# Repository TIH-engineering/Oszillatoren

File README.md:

# LA – Oszillatoren

## 🔌 Leiterplattenbeschreibung

Die Leiterplatte **LA – Oszillatoren** wurde für Laborübungen im Bereich
Elektronik und Hardwareentwicklung entwickelt. Sie ermöglicht die praktische
Untersuchung unterschiedlicher Oszillatorschaltungen und den Vergleich ihrer
Funktionsprinzipien und Eigenschaften.

Auf einer gemeinsamen Leiterplatte sind mehrere typische Oszillatorschaltungen
realisiert:

- **RC-Phasenschieber-Oszillator**
- **Wien-Brücken-Oszillator**
- **OPV-Relaxationsoszillator**
- **RC-/Quarzoszillatoren**

Die Schaltungen sind räumlich voneinander getrennt aufgebaut und verfügen über
gut zugängliche Messpunkte. Dadurch können charakteristische Signale direkt mit
dem Oszilloskop untersucht und mit den theoretisch berechneten Größen verglichen
werden.

Bei ausgewählten Schaltungen sind Bauteile steck- bzw. austauschbar ausgeführt.
Damit können beispielsweise unterschiedliche Widerstandswerte eingesetzt und
deren Einfluss auf Frequenz und Schwingverhalten experimentell untersucht werden.

Die Leiterplatte wird mit **+5 V / GND / −5 V** versorgt. Die einzelnen
Messpunkte und Anschlüsse sind direkt auf der Leiterplatte beschriftet.

> **Einsatzgebiet:** Laborunterricht zur Untersuchung von Oszillatoren,
> Schwingbedingungen, Frequenzbestimmung und dem Einfluss einzelner Bauteile.

---

# 📥 Downloads

| Datei | Beschreibung |
|:------|:-------------|
| 📄 Schaltplan (PDF) | [`schematic.pdf`](../../releases/latest/download/schematic.pdf) |
| 🖨 Leiterplatte (PDF) | [`pcb.pdf`](../../releases/latest/download/pcb.pdf) |
| 🔩 Bohrplan | [`drill.pdf`](../../releases/latest/download/drill.pdf) |
| 📋 Stückliste (Excel) | [`bom.xlsx`](../../releases/latest/download/bom.xlsx) |
| 🌐 Interactive BOM | [`ibom.html`](../../releases/latest/download/ibom.html) |
| 📦 Fertigungsdaten | [`kicad.zip`](../../releases/latest/download/kicad.zip) |
| 🧊 STEP-Modell | [`pcb.step`](../../releases/latest/download/pcb.step) |

---

# 🖥 Leiterplatte

## Vorschau

| Oberseite | Unterseite |
|:---------:|:----------:|
|  |  |

## Oberseite

## Unterseite

---

# ℹ Projektinformationen

| Eigenschaft | Wert |
|--------------|------|
| Projekt | LA – Oszillatoren |
| Software | KiCad 10 |
| Repository | TIH-engineering/Oszillatoren |
| Lizenz | CC BY-NC-SA 4.0 |

---

# 🚀 Releases

Jeder Release enthält automatisch:

- Gerberdaten
- Bohrdaten
- Stückliste (Excel)
- Interactive BOM
- STEP-Modell
- Schaltplan als PDF
- Leiterplatte als PDF
- 3D-Renderings

Die jeweils aktuelle Version befindet sich unter **Releases**.

---

# 👨‍🏫 Autor

**HTL Rankweil**  
Labor Elektronik / Hardwareentwicklung

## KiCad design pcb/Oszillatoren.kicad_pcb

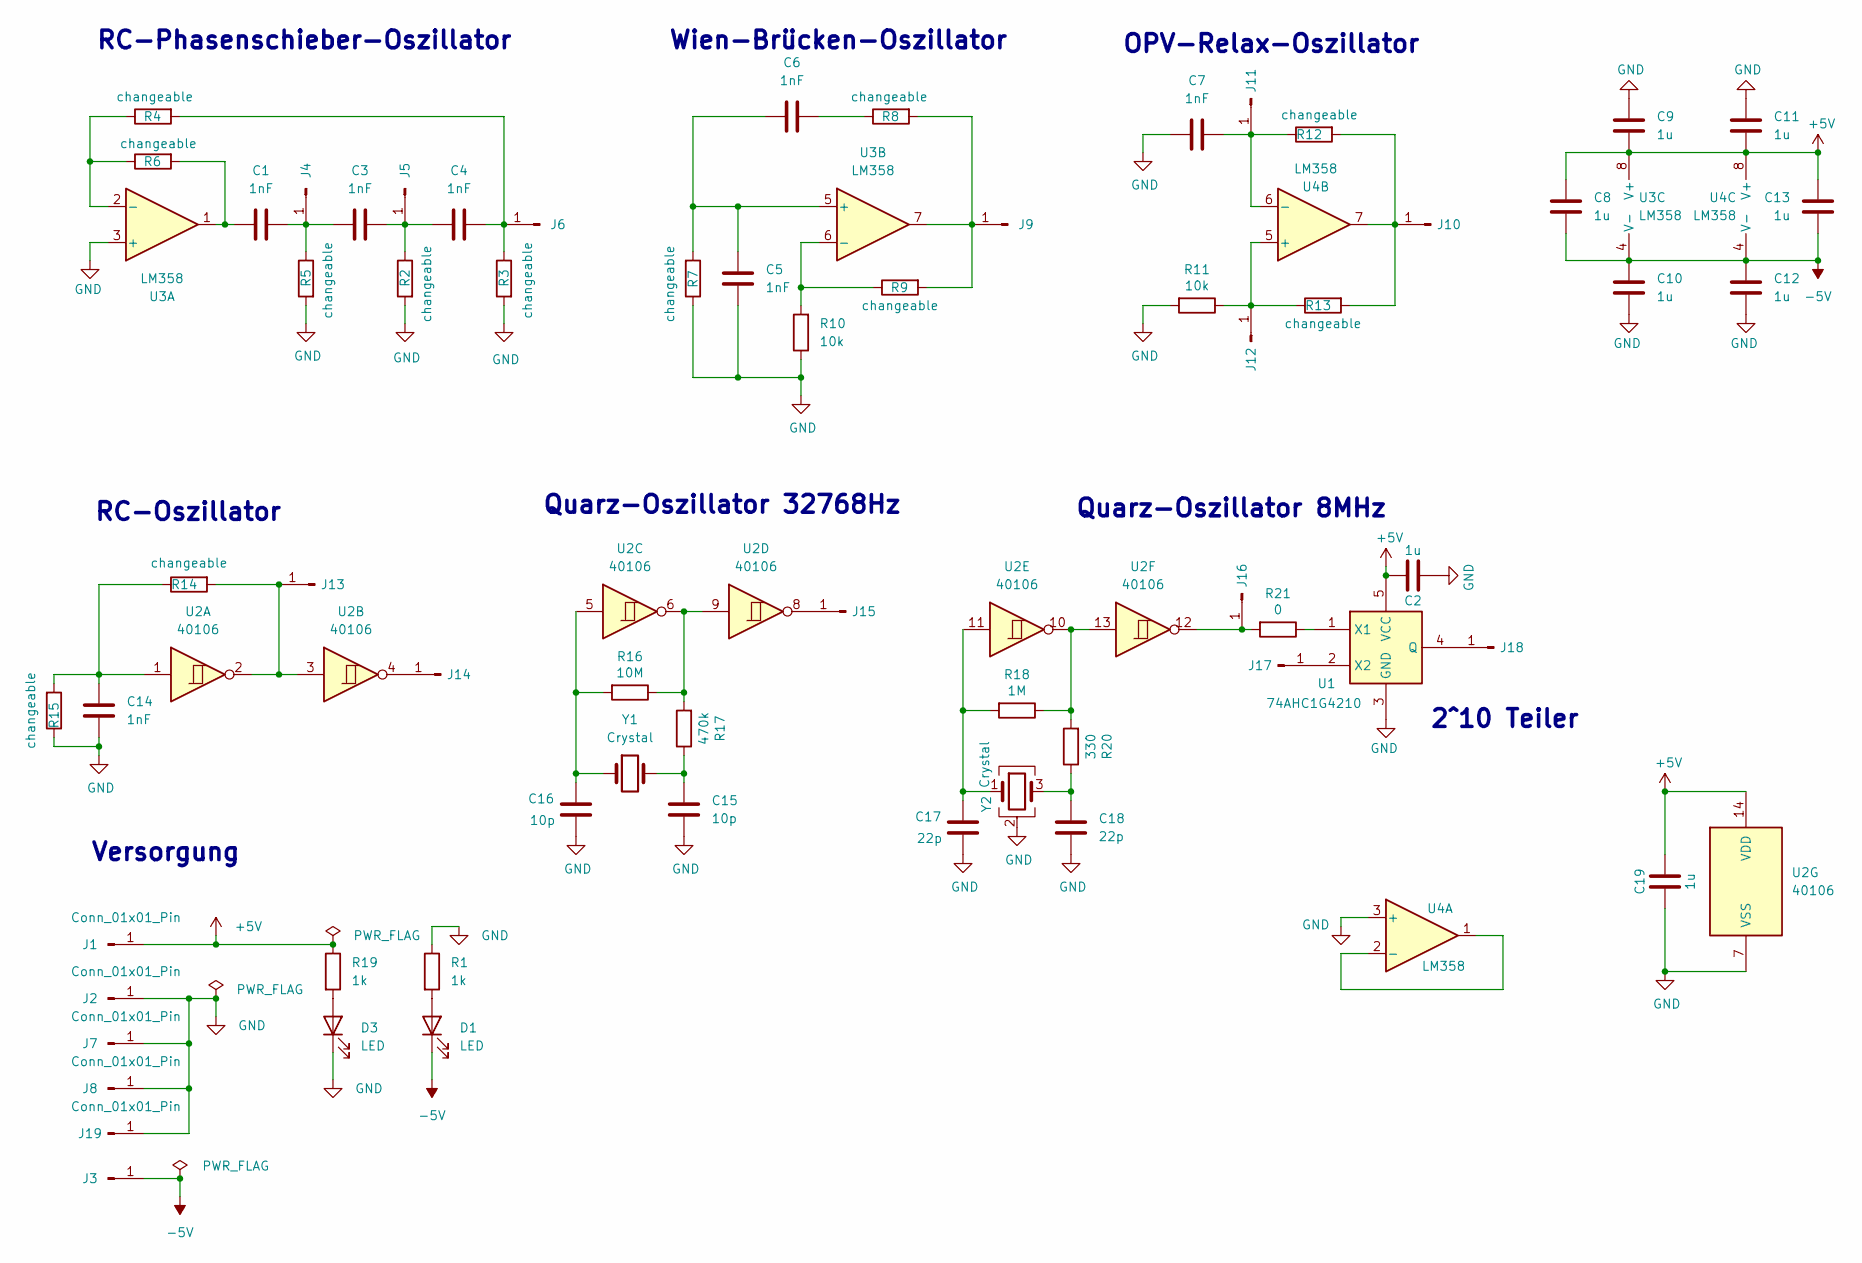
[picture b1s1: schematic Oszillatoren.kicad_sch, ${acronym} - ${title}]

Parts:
C1, C3, C4, C5, C6, C7, C14: 1nF; C_0805_2012Metric
C2, C8, C9, C10, C11, C12, C13, C19: 1u; C_1206_3216Metric
C15, C16: 10p; C_0603_1608Metric
C17, C18: 22p; C_0603_1608Metric
D1, D3: LED; LED_1206_3216Metric
J1, J2, J3, J4, J5, J6, J7, J8, J9, J10, J11, J12, J13, J14, J15, J16, J17, J18, J19: Conn_01x01_Pin; PinHeader_1x01_P2.54mm_Vertical
R1, R19: 1k; R_1206_3216Metric
R2, R3, R4, R5, R6, R7, R8, R9, R12, R13, R14, R15: 10k; R_axial_SMD-Adapter_P10.16mm_1mm
R10, R11: 10k; R_0805_2012Metric
R16: 10M; R_0805_2012Metric
R17: 470k; R_0805_2012Metric
R18: 1M; R_0805_2012Metric
R20: 330; R_0805_2012Metric
R21: 0; R_0805_2012Metric
U1: 74AHC1G4210; SOT-353_SC-70-5
U2: 40106; DIP-14_W7.62mm
U3, U4: LM358; DIP-8_W7.62mm
Y1: Crystal; Crystal_SMD_G8-2Pin_3.2x1.5mm_HandSoldering
Y2: Crystal; Crystal_SMD_EuroQuartz_MQ-4Pin_7.0x5.0mm_HandSoldering

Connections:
+5V: C2.1, C8.1, C9.1, C11.2, C13.1, C19.1, J1.1 (Pin_1_1), R19.1, U1.5 (VCC), U2.14 (VDD), U3.8 (V+), U4.8 (V+)
-5V: C8.2, C10.2, C12.1, C13.2, D1.1 (K), J3.1 (Pin_1_1), U3.4 (V-), U4.4 (V-)
GND: C2.2, C5.1, C7.2, C9.2, C10.1, C11.1, C12.2, C14.1, C15.2, C16.2, C17.2, C18.2, C19.2, D3.1 (K), J2.1 (Pin_1_1), J7.1 (Pin_1_1), J8.1 (Pin_1_1), J19.1 (Pin_1_1), R1.1, R2.2, R3.2, R5.2, R7.1, R10.1, R11.2, R15.1, U1.3 (GND), U2.7 (VSS), U3.3 (+), U4.3 (+), Y2.2 (G), Y2.4 (G)
unnamed: C1.1, R6.2, U3.1
unnamed: C6.2, R8.1
unnamed: C14.2, R14.1, R15.2, U2.1
unnamed: C15.1, R17.1, Y1.2
unnamed: C16.1, R16.2, U2.5, Y1.1
unnamed: C17.1, R18.2, U2.11, Y2.1
unnamed: C18.1, R20.1, Y2.3
unnamed: D1.2 (A), R1.2
unnamed: D3.2 (A), R19.2
unnamed: C1.2, C3.1, J4.1 (Pin_1_1), R5.1
unnamed: C3.2, C4.1, J5.1 (Pin_1_1), R2.1
unnamed: C4.2, J6.1 (Pin_1_1), R3.1, R4.2
unnamed: J9.1 (Pin_1_1), R8.2, R9.2, U3.7
unnamed: J10.1 (Pin_1_1), R12.2, R13.2, U4.7
unnamed: C7.1, J11.1 (Pin_1_1), R12.1, U4.6 (-)
unnamed: J12.1 (Pin_1_1), R11.1, R13.1, U4.5 (+)
unnamed: J13.1 (Pin_1_1), R14.2, U2.2, U2.3
unnamed: J14.1 (Pin_1_1), U2.4
unnamed: J15.1 (Pin_1_1), U2.8
unnamed: J16.1 (Pin_1_1), R21.2, U2.12
unnamed: J17.1 (Pin_1_1), U1.2 (X2)
unnamed: J18.1 (Pin_1_1), U1.4 (Q)
unnamed: R16.1, R17.2, U2.6, U2.9
unnamed: R18.1, R20.2, U2.10, U2.13
unnamed: R21.1, U1.1 (X1)
unnamed: R4.1, R6.1, U3.2 (-)
unnamed: C5.2, C6.1, R7.2, U3.5 (+)
unnamed: R9.1, R10.2, U3.6 (-)
unnamed: U4.1, U4.2 (-)

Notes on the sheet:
2^10 Teiler
RC-Oszillator
Versorgung
OPV-Relax-Oszillator
RC-Phasenschieber-Oszillator
Wien-Brücken-Oszillator
Quarz-Oszillator 8MHz
Quarz-Oszillator 32768Hz

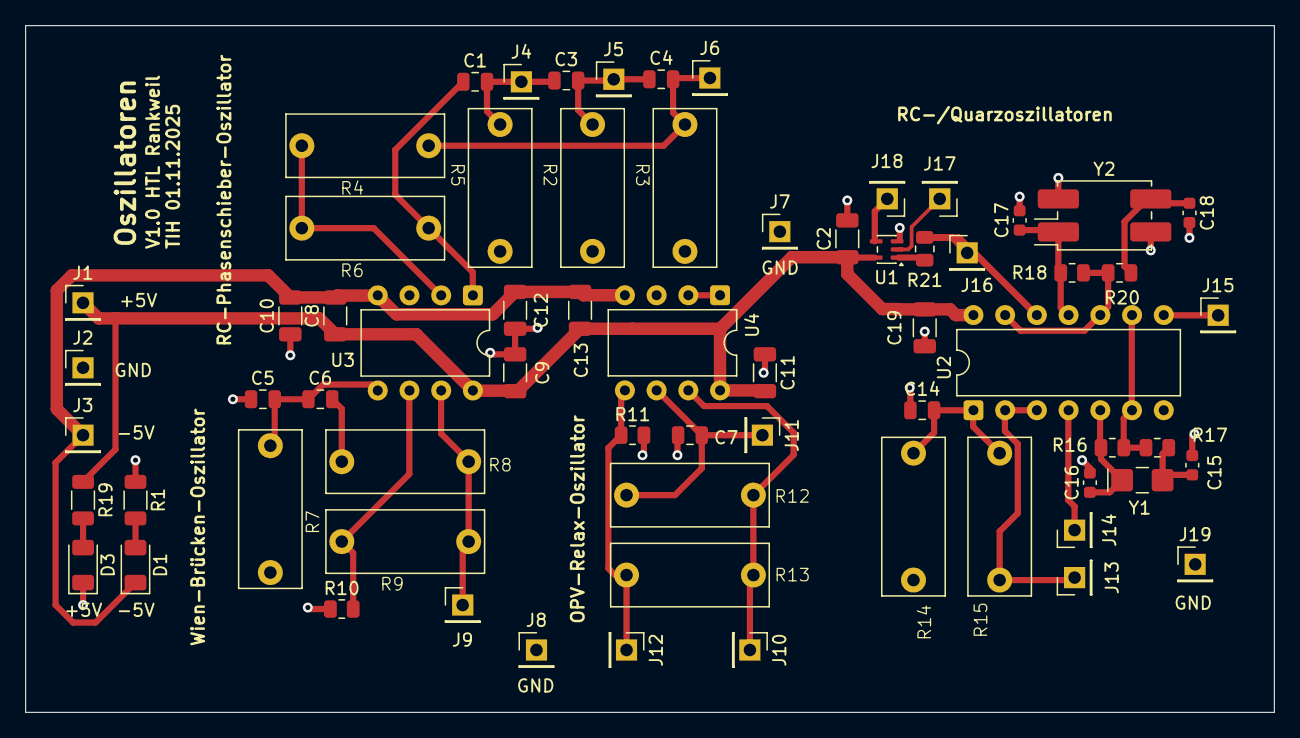
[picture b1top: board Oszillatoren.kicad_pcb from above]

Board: 2 copper layers, 100.0 x 55.0 mm, 67 parts (0 on the bottom side), 32 nets.

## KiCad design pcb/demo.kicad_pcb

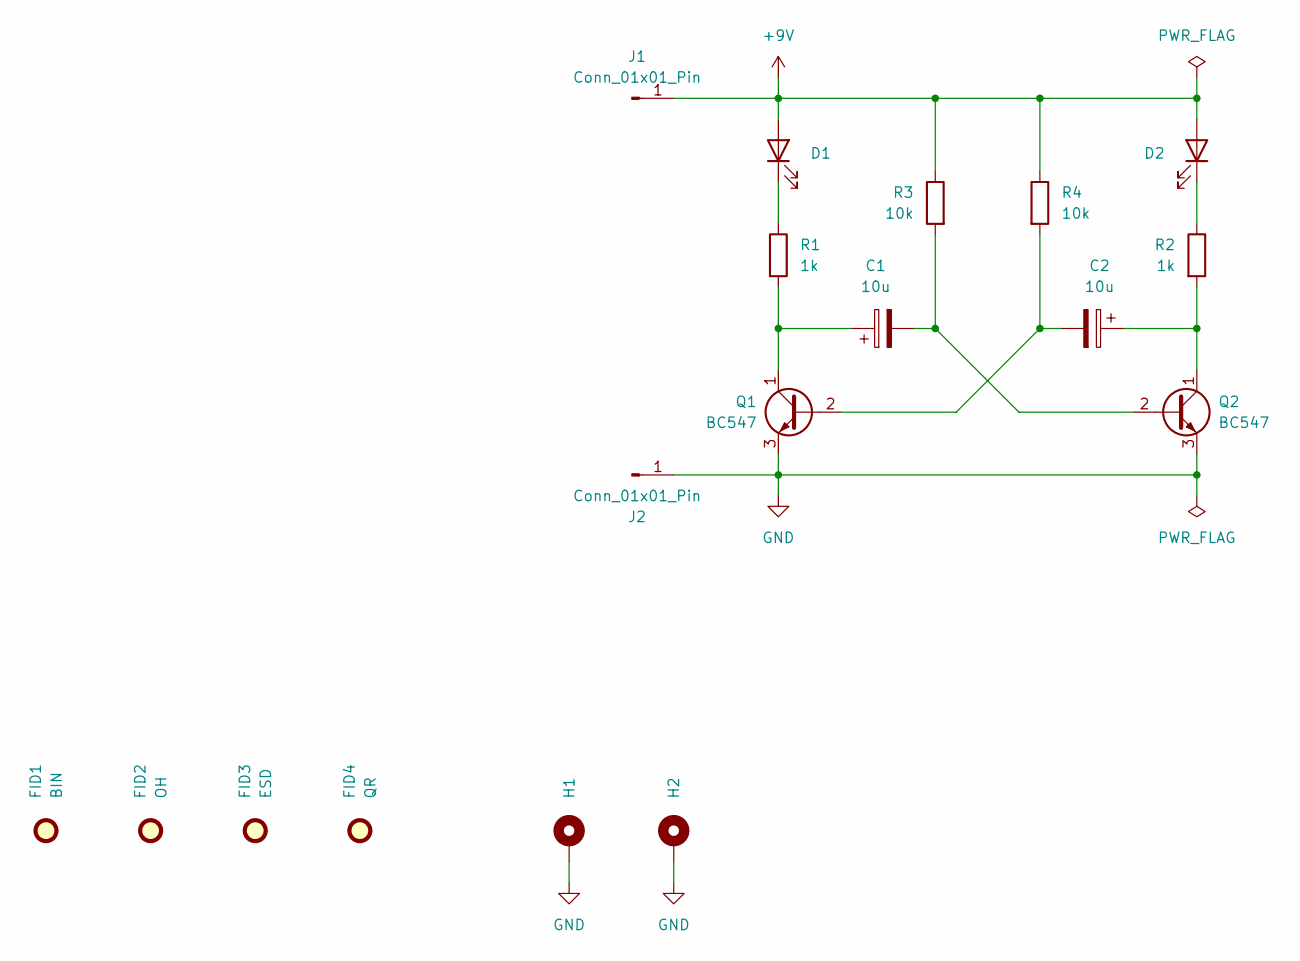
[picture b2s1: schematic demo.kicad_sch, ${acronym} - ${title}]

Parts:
C1, C2: 10u; CP_Radial_D4.0mm_P2.00mm
D1, D2: LED; LED_D5.0mm
FID1: BIN; WEEE-Logo_4.2x6mm_SilkScreen
FID2: OH; OSHW-Logo2_7.3x6mm_SilkScreen
FID3: ESD; ESD-Logo_6.6x6mm_SilkScreen
FID4: QR; QR_0x007e
H1, H2: MountingHole_Pad; MountingHole_3.2mm_M3_DIN965_Pad
J1, J2: Conn_01x01_Pin; PinHeader_1x01_P2.54mm_Vertical
Q1, Q2: BC547; TO-92L_Inline_Wide
R1, R2: 1k; R_Axial_DIN0207_L6.3mm_D2.5mm_P10.16mm_Horizontal
R3, R4: 10k; R_Axial_DIN0207_L6.3mm_D2.5mm_P10.16mm_Horizontal

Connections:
+9V: D1.2 (A), D2.2 (A), J1.1, R3.1, R4.1
GND: H1.1, H2.1, J2.1, Q1.3 (E), Q2.3 (E)
unnamed: D1.1 (K), R1.1
unnamed: D2.1 (K), R2.1
unnamed: C2.2, Q1.2 (B), R4.2
unnamed: C1.1, Q1.1 (C), R1.2
unnamed: C1.2, Q2.2 (B), R3.2
unnamed: C2.1, Q2.1 (C), R2.2

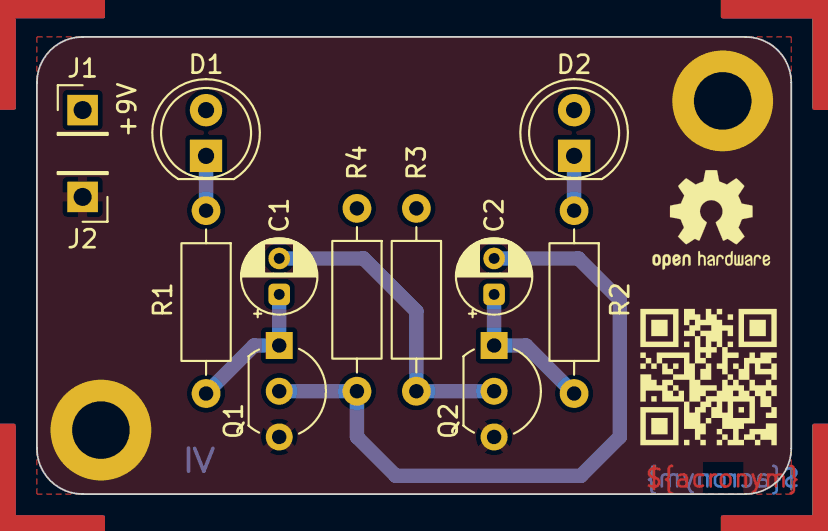
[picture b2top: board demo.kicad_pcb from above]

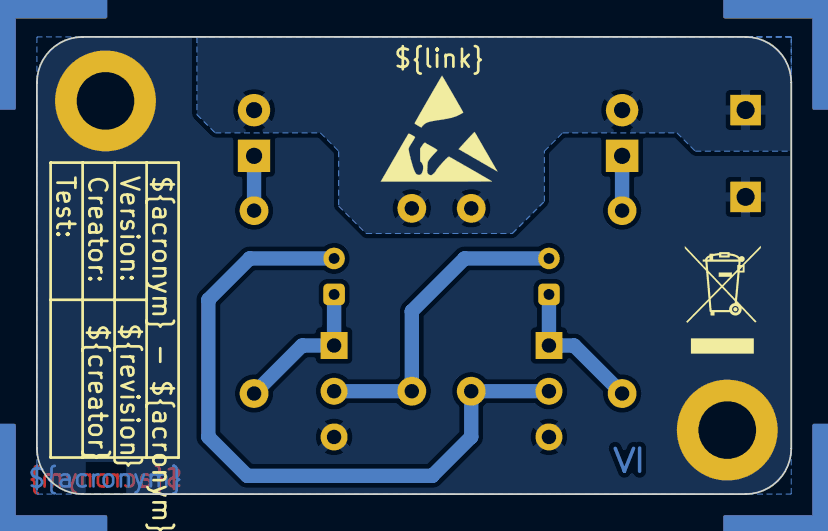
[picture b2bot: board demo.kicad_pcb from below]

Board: 2 copper layers, 41.9 x 25.4 mm, 18 parts (2 on the bottom side), 8 nets.

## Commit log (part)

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2026-06-22 Replace demo project with Oszillatoren
2026-06-22 build und release angepasst Oszillatoren statt demo
2026-06-22 template schematic A4-landscape directory changed
2026-06-22 directory-change saved (landscape)
2026-06-22 footprint-library TIH added

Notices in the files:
parts and their libraries:
license: CC BY-NC-SA 4.0
